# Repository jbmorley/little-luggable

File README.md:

# Little Luggable

Raspberry Pi Cyberdeck

## Overview

The Little Luggable is my take on a cyberdeck. It's built around the [Raspberry Pi 5](https://www.raspberrypi.com/products/raspberry-pi-5/) and the [Pelican 1150 Protector Case](https://www.peli.com/eu/en/product/cases/protector/1150). It includes a [fully-custom mechanical keyboard](/docs/keyboard) designed to perfectly fit the lid of the 1150.

Check out the [project page](https://little-luggable.jbmorley.co.uk) for more.

# License

Little Luggable is Copyright (c) 2022-2026 Jason Morley (see [COPYRIGHT](https://github.com/jbmorley/little-luggable/blob/main/COPYRIGHT)) and licensed under the [Creative Commons Attribution 4.0 International License](https://creativecommons.org/licenses/by/4.0/) (see [LICENSE](https://github.com/jbmorley/little-luggable/blob/main/LICENSE)). Unless otherwise stated, photographs are Copyright (c) 2026 [Mar Mizunaka](http://marmizunaka.com), and cannot be reproduced without permission.

The Little Luggable depends on the following separately licensed third-party libraries and components:

- [Keebio Components](https://github.com/keebio/keebio-components), MIT License
- [Keebio-Parts.pretty](https://github.com/keebio/Keebio-Parts.pretty), MIT License
- [marbastlib](https://github.com/ebastler/marbastlib), CERN Open Hardware Licence Version 2 – Permissive
- [Nabla](https://fonts.google.com/specimen/Nabla), SIL Open Font License 1.1
- [Recursive](https://fonts.google.com/specimen/Recursive), SIL Open Font License 1.1
- [ZMK](https://github.com/zmkfirmware/zmk), MIT License

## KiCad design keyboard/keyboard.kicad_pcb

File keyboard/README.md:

# Keyboard

## Design

The Little Luggable features a custom 64-key keyboard that I created with the very specific goal of deviating as little as possible from a standard keyboard layout.

The basic design was created using [Keyboard Layout Editor](http://www.keyboard-layout-editor.com) and the JSON can be found in `keyboard/layouts`.

### Base Layer

### Lower Layer (Bluetooth Controls)

### Raise Layer (Punctuation and Special Characters)

## Useful References

- [YouTube – Making a Keyboard Macropad PCB (Kicad 6.0), Noah Kiser](https://www.youtube.com/watch?v=7O8xGd7Pd88)
- [YouTube – Single Button Nice!Nano Keyboard, Ben Vallack](https://www.youtube.com/watch?v=vr8LkjsRqZs)
- [YouTube – Make your own analog keyboard PCB (in Kicad) - Part 1 (Schematic), riskable](https://www.youtube.com/watch?v=TfKz_FbZWLQ)
- [Broaching Standoff](https://www.youtube.com/watch?v=TuJRveLrtYI)
- [Broaching nuts and standoffs](https://www.inserco.eu/en/broaching-inserts-ipcbricbfhiscbr/)
- [Solderable threaded inserts?](https://www.designdevelopmenttoday.com/new-products/fastening-assembly/fastening-assembly/product/21092287/keystone-electronics-corp-zero-height-threaded-inserts-for-pc-boards)
- [Keyswitch Kicad Library](https://github.com/perigoso/keyswitch-kicad-library)

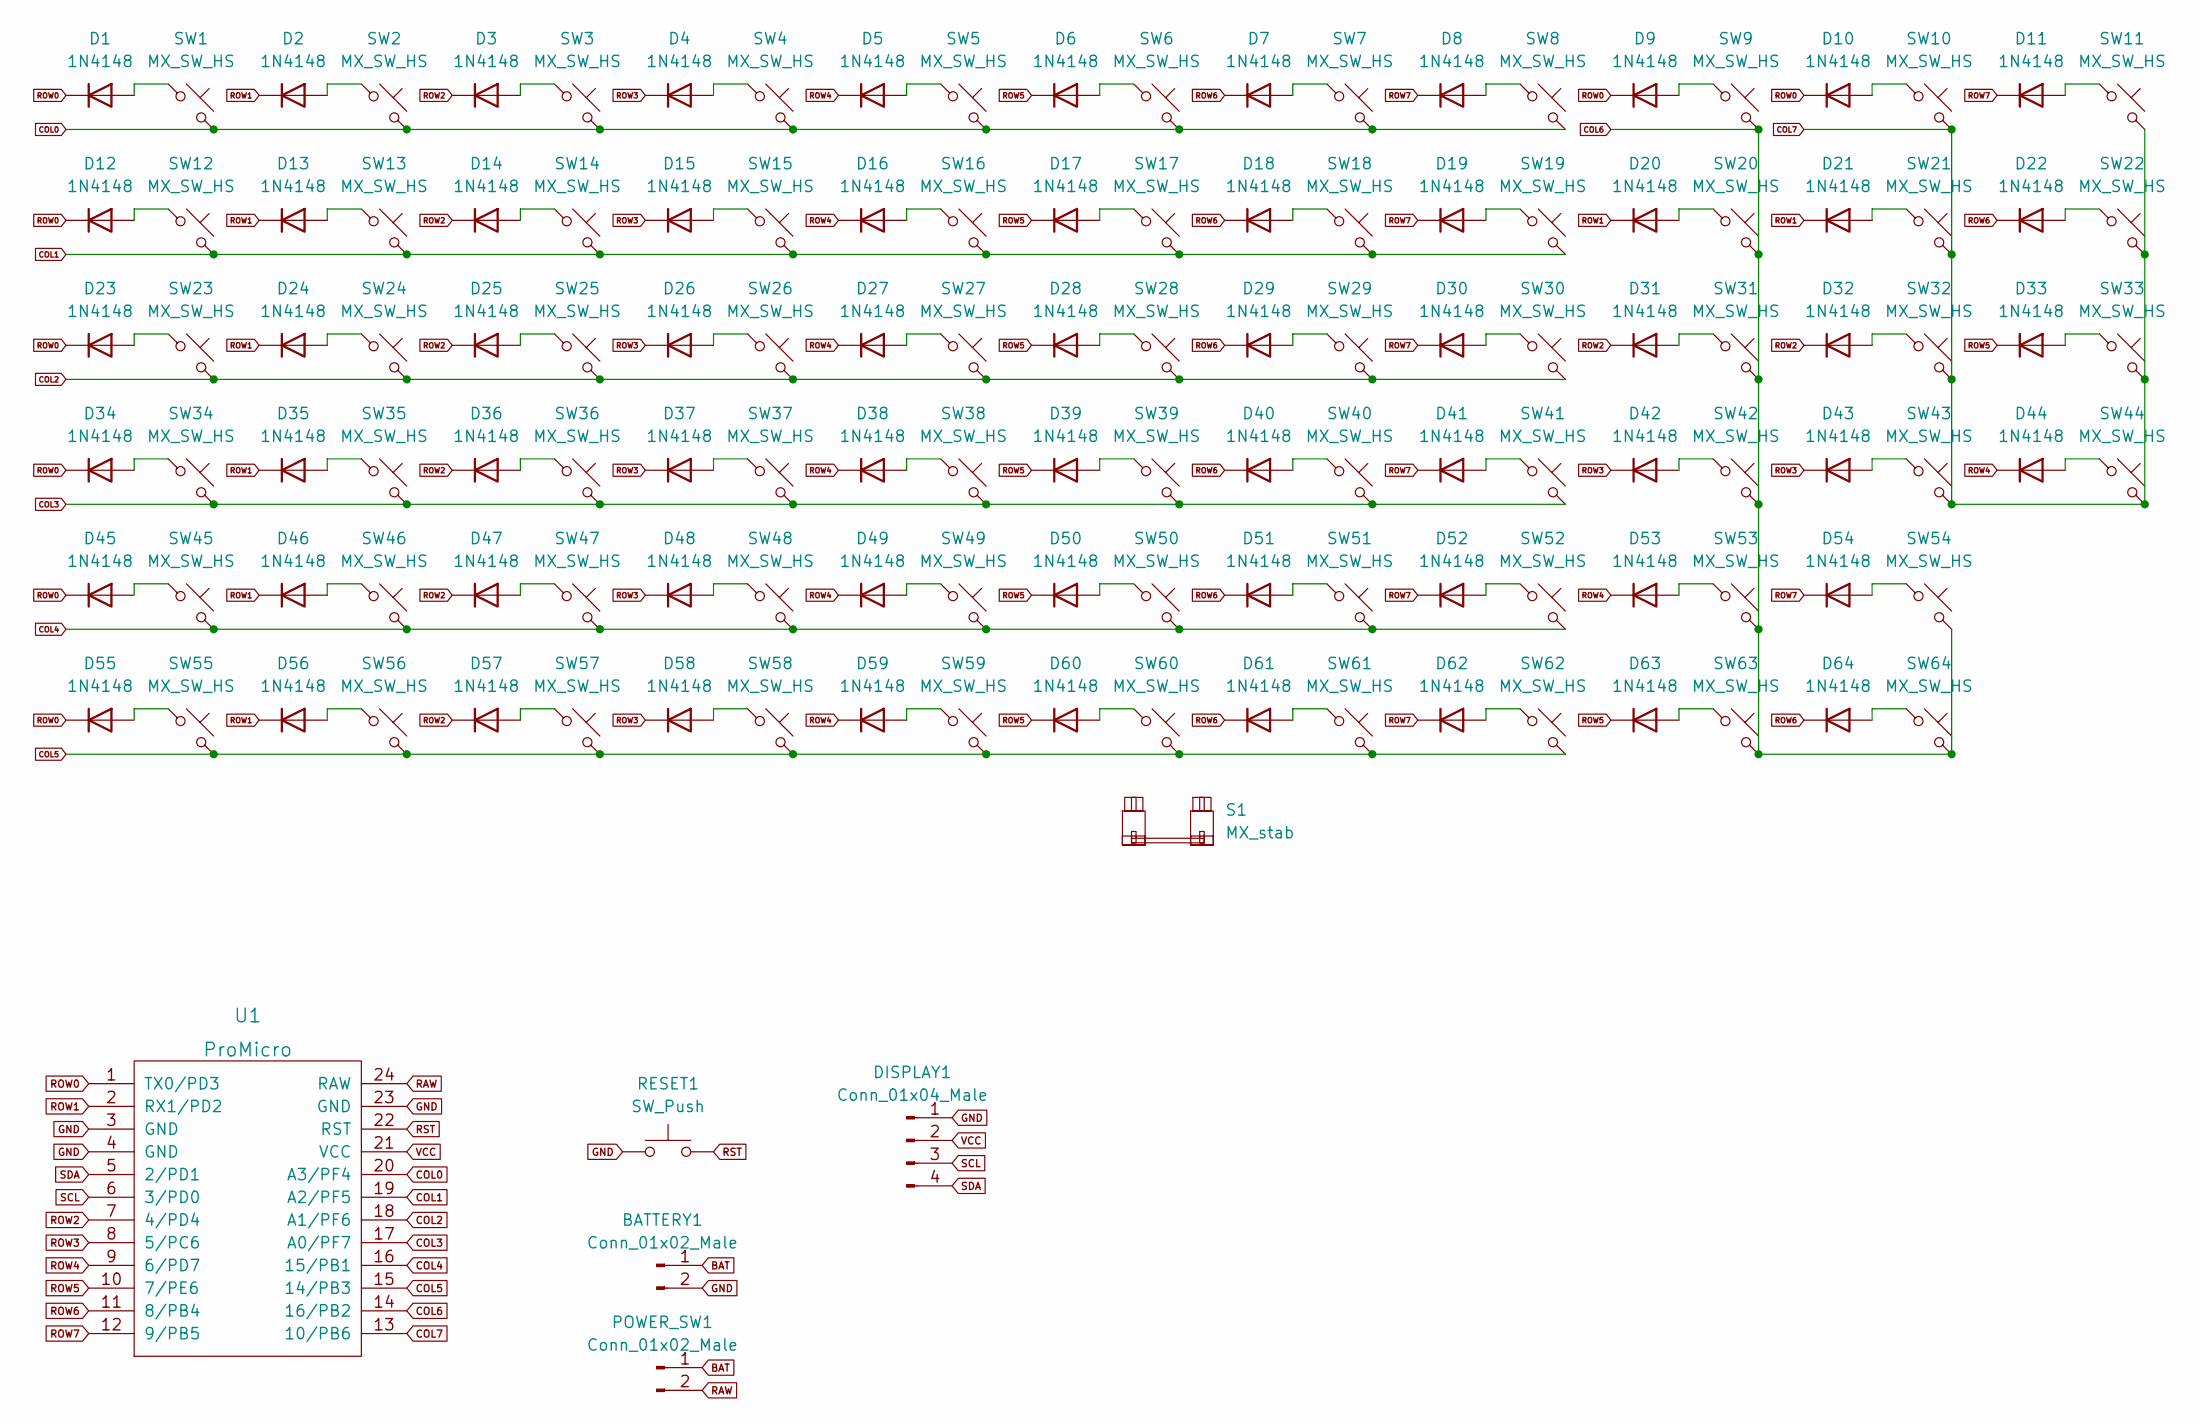
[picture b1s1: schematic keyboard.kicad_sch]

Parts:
BATTERY1: Conn_01x02_Male; PinHeader_1x02_P2.54mm_Vertical
D1, D2, D3, D4, D5, D6, D7, D8, D9, D10, D11, D12, D13, D14, D15, D16, D17, D18, D19, D20, D21, D22, D23, D24, D25, D26, D27, D28, D29, D30, D31, D32, D33, D34, D35, D36, D37, D38, D39, D40, D41, D42, D43, D44, D45, D46, D47, D48, D49, D50, D51, D52, D53, D54, D55, D56, D57, D58, D59, D60, D61, D62, D63, D64: 1N4148; D_DO-35_SOD27_P7.62mm_Horizontal
DISPLAY1: Conn_01x04_Male; PinHeader_1x04_P2.54mm_Vertical
POWER_SW1: Conn_01x02_Male; PinHeader_1x02_P2.54mm_Horizontal
RESET1: SW_Push; SW_PUSH_6mm_H13mm
S1: MX_stab; STAB_MX_P_2u
SW1, SW2, SW3, SW4, SW5, SW6, SW7, SW8, SW9, SW10, SW11, SW12, SW13, SW14, SW15, SW16, SW17, SW18, SW19, SW20, SW21, SW22, SW23, SW24, SW25, SW26, SW27, SW28, SW29, SW30, SW31, SW32, SW33, SW34, SW35, SW36, SW37, SW38, SW39, SW40, SW41, SW42, SW43, SW44, SW45, SW46, SW47, SW48, SW49, SW50, SW51, SW52, SW53, SW54, SW55, SW56, SW57, SW58, SW59, SW60, SW61, SW62, SW63, SW64: MX_SW_HS; SW_MX_HS_1u
U1: ProMicro; ArduinoProMicro

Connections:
BAT: BATTERY1.1, POWER_SW1.1; also elsewhere on the board
COL0: SW1.2, SW2.2, SW3.2, SW4.2, SW5.2, SW6.2, SW7.2, SW8.2, U1.20 (A3/PF4)
COL1: SW12.2, SW13.2, SW14.2, SW15.2, SW16.2, SW17.2, SW18.2, SW19.2, U1.19 (A2/PF5)
COL2: SW23.2, SW24.2, SW25.2, SW26.2, SW27.2, SW28.2, SW29.2, SW30.2, U1.18 (A1/PF6)
COL3: SW34.2, SW35.2, SW36.2, SW37.2, SW38.2, SW39.2, SW40.2, SW41.2, U1.17 (A0/PF7)
COL4: SW45.2, SW46.2, SW47.2, SW48.2, SW49.2, SW50.2, SW51.2, SW52.2, U1.16 (15/PB1)
COL5: SW55.2, SW56.2, SW57.2, SW58.2, SW59.2, SW60.2, SW61.2, SW62.2, U1.15 (14/PB3)
COL6: SW9.2, SW20.2, SW31.2, SW42.2, SW53.2, SW54.2, SW63.2, SW64.2, U1.14 (16/PB2)
COL7: SW10.2, SW11.2, SW21.2, SW22.2, SW32.2, SW33.2, SW43.2, SW44.2, U1.13 (10/PB6)
GND: BATTERY1.2, DISPLAY1.1, RESET1.1, U1.3 (GND), U1.4 (GND), U1.23 (GND); also elsewhere on the board
unnamed: D1.2 (A), SW1.1
unnamed: D2.2 (A), SW2.1
unnamed: D3.2 (A), SW3.1
unnamed: D4.2 (A), SW4.1
unnamed: D5.2 (A), SW5.1
unnamed: D6.2 (A), SW6.1
unnamed: D7.2 (A), SW7.1
unnamed: D8.2 (A), SW8.1
unnamed: D9.2 (A), SW9.1
unnamed: D10.2 (A), SW10.1
unnamed: D11.2 (A), SW11.1
unnamed: D12.2 (A), SW12.1
unnamed: D13.2 (A), SW13.1
unnamed: D14.2 (A), SW14.1
unnamed: D15.2 (A), SW15.1
unnamed: D16.2 (A), SW16.1
unnamed: D17.2 (A), SW17.1
unnamed: D18.2 (A), SW18.1
unnamed: D19.2 (A), SW19.1
unnamed: D20.2 (A), SW20.1
unnamed: D21.2 (A), SW21.1
unnamed: D22.2 (A), SW22.1
unnamed: D23.2 (A), SW23.1
unnamed: D24.2 (A), SW24.1
unnamed: D25.2 (A), SW25.1
unnamed: D26.2 (A), SW26.1
unnamed: D27.2 (A), SW27.1
unnamed: D28.2 (A), SW28.1
unnamed: D29.2 (A), SW29.1
unnamed: D30.2 (A), SW30.1
unnamed: D31.2 (A), SW31.1
unnamed: D32.2 (A), SW32.1
unnamed: D33.2 (A), SW33.1
unnamed: D34.2 (A), SW34.1
unnamed: D35.2 (A), SW35.1
unnamed: D36.2 (A), SW36.1
unnamed: D37.2 (A), SW37.1
unnamed: D38.2 (A), SW38.1
unnamed: D39.2 (A), SW39.1
unnamed: D40.2 (A), SW40.1
unnamed: D41.2 (A), SW41.1
unnamed: D42.2 (A), SW42.1
unnamed: D43.2 (A), SW43.1
unnamed: D44.2 (A), SW44.1
unnamed: D45.2 (A), SW45.1
unnamed: D46.2 (A), SW46.1
unnamed: D47.2 (A), SW47.1
unnamed: D48.2 (A), SW48.1
unnamed: D49.2 (A), SW49.1
unnamed: D50.2 (A), SW50.1
unnamed: D51.2 (A), SW51.1
unnamed: D52.2 (A), SW52.1
unnamed: D53.2 (A), SW53.1
unnamed: D54.2 (A), SW54.1
unnamed: D55.2 (A), SW55.1
unnamed: D56.2 (A), SW56.1
unnamed: D57.2 (A), SW57.1
unnamed: D58.2 (A), SW58.1
unnamed: D59.2 (A), SW59.1
unnamed: D60.2 (A), SW60.1
unnamed: D61.2 (A), SW61.1
unnamed: D62.2 (A), SW62.1
unnamed: D63.2 (A), SW63.1
unnamed: D64.2 (A), SW64.1
RAW: POWER_SW1.2, U1.24 (RAW); also elsewhere on the board
ROW0: D1.1 (K), D9.1 (K), D10.1 (K), D12.1 (K), D23.1 (K), D34.1 (K), D45.1 (K), D55.1 (K), U1.1 (TX0/PD3)
ROW1: D2.1 (K), D13.1 (K), D20.1 (K), D21.1 (K), D24.1 (K), D35.1 (K), D46.1 (K), D56.1 (K), U1.2 (RX1/PD2)
ROW2: D3.1 (K), D14.1 (K), D25.1 (K), D31.1 (K), D32.1 (K), D36.1 (K), D47.1 (K), D57.1 (K), U1.7 (4/PD4)
ROW3: D4.1 (K), D15.1 (K), D26.1 (K), D37.1 (K), D42.1 (K), D43.1 (K), D48.1 (K), D58.1 (K), U1.8 (5/PC6)
ROW4: D5.1 (K), D16.1 (K), D27.1 (K), D38.1 (K), D44.1 (K), D49.1 (K), D53.1 (K), D59.1 (K), U1.9 (6/PD7)
ROW5: D6.1 (K), D17.1 (K), D28.1 (K), D33.1 (K), D39.1 (K), D50.1 (K), D60.1 (K), D63.1 (K), U1.10 (7/PE6)
ROW6: D7.1 (K), D18.1 (K), D22.1 (K), D29.1 (K), D40.1 (K), D51.1 (K), D61.1 (K), D64.1 (K), U1.11 (8/PB4)
ROW7: D8.1 (K), D11.1 (K), D19.1 (K), D30.1 (K), D41.1 (K), D52.1 (K), D54.1 (K), D62.1 (K), U1.12 (9/PB5)
RST: RESET1.2, U1.22 (RST); also elsewhere on the board
SCL: DISPLAY1.3, U1.6 (3/PD0); also elsewhere on the board
SDA: DISPLAY1.4, U1.5 (2/PD1); also elsewhere on the board
VCC: DISPLAY1.2, U1.21 (VCC); also elsewhere on the board

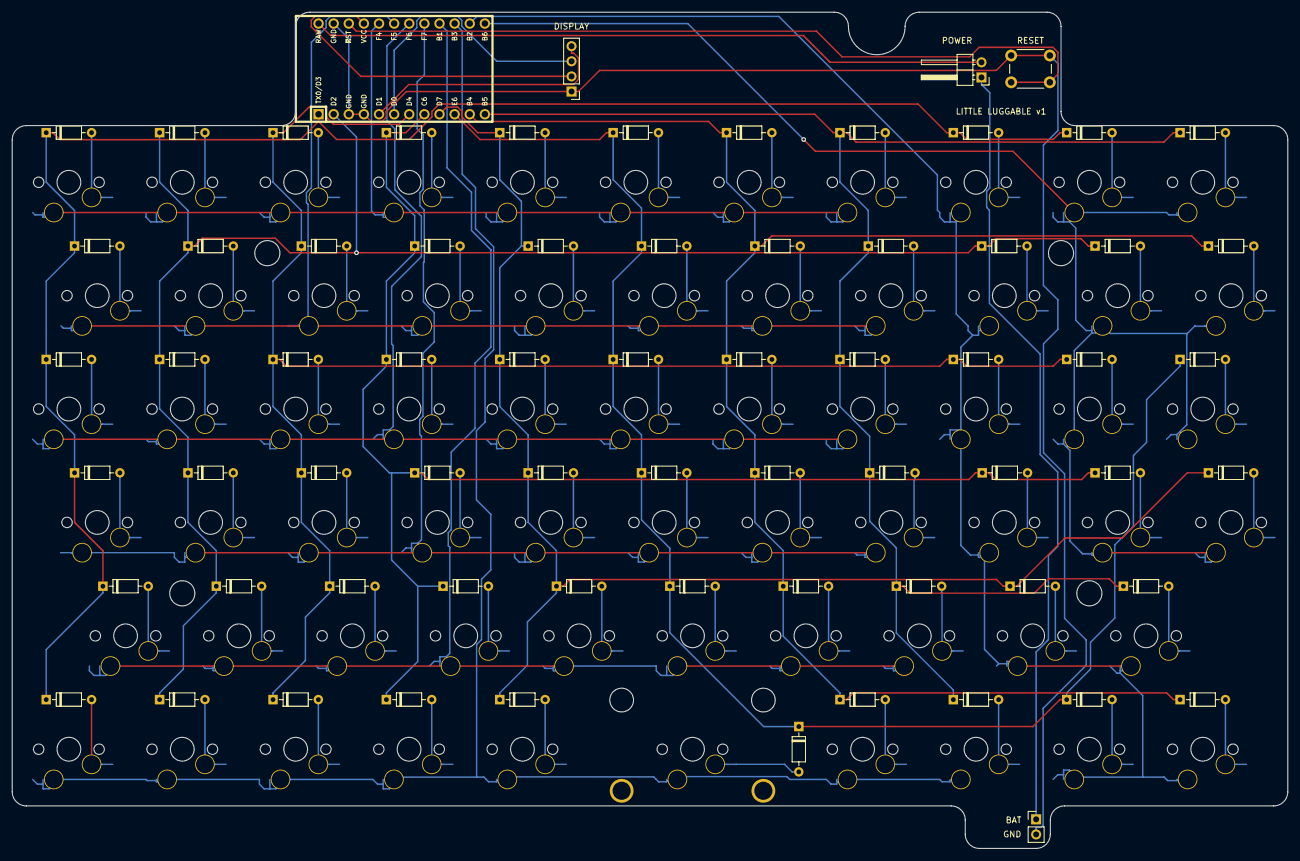
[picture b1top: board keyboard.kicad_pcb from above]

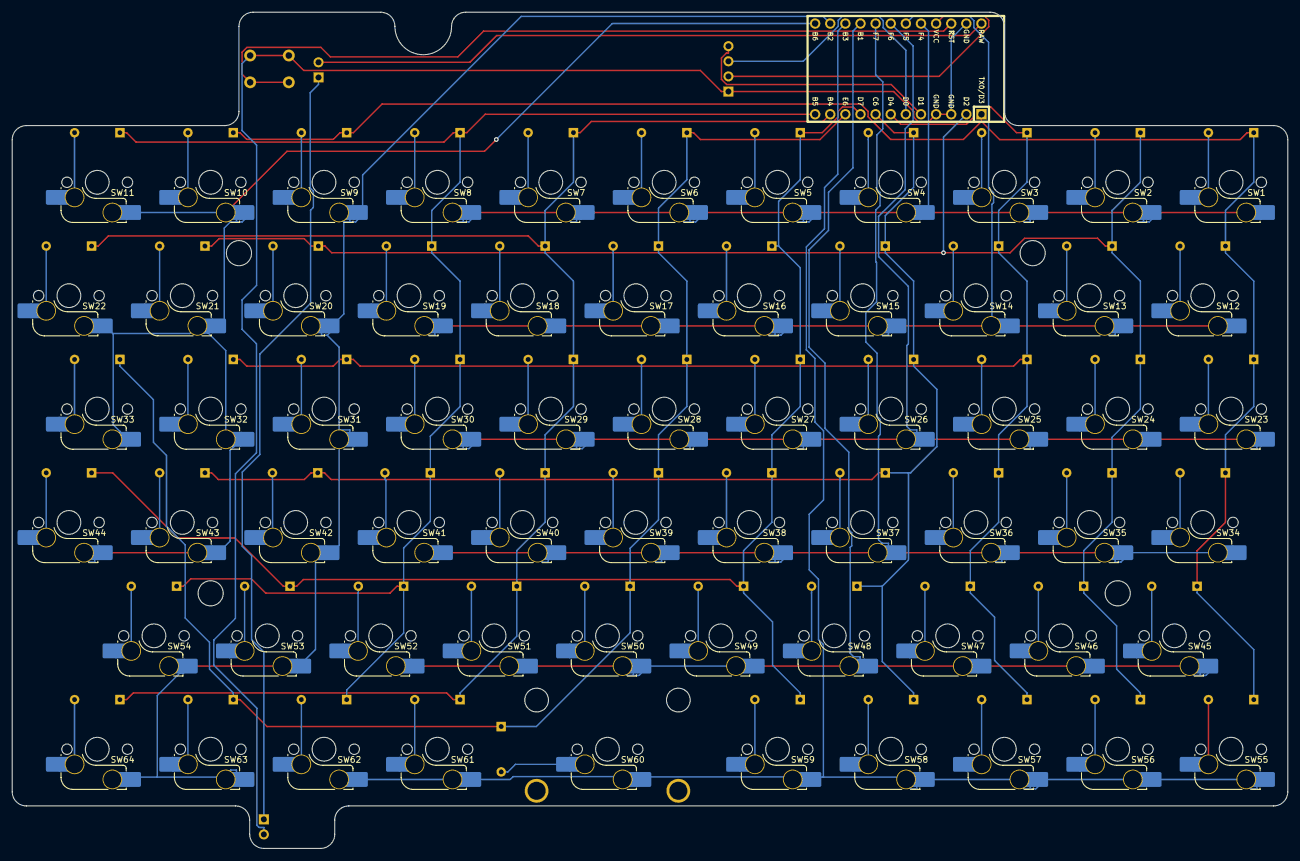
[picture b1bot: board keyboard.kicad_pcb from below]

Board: 2 copper layers, 214.3 x 140.5 mm, 134 parts (64 on the bottom side), 87 nets.

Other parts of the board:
DISPLAY: Conn_01x04_Male; PinHeader_1x04_P2.54mm_Vertical
POWER: Conn_01x02_Male; PinHeader_1x02_P2.54mm_Horizontal
RESET: SW_Push; SW_PUSH_6mm_H13mm

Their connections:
BAT: POWER.1; also elsewhere on the board
GND: DISPLAY.1, RESET.1; also elsewhere on the board
RAW: POWER.2; also elsewhere on the board
RST: RESET.2; also elsewhere on the board
SCL: DISPLAY.3; also elsewhere on the board
SDA: DISPLAY.4; also elsewhere on the board
VCC: DISPLAY.2; also elsewhere on the board

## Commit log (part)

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2023-02-15 Add the raise
2023-02-15 Correct the raise
2023-02-15 Add tilde
2023-02-16 Update the description and hero image
2023-02-16 Clean up the ideas
2023-02-16 Update the description
2023-02-16 Update the nice!nano link
2023-02-16 Clean up the keyboard parts table
2023-02-16 Clean up the main parts table
2023-02-16 Move some of the keyboard notes into a separate file
2023-02-16 Clearer 'Useful References' section
2023-02-16 Re-order the PiJuice and battery
2023-02-16 Add settings for laser cutting with Betsy
2023-02-16 Add footnote on laser cutter settings
2023-02-16 Add the keycaps
2023-02-16 Add the Kailh hotswap sockets
2023-02-16 Add brief description to the keyboard page
2023-02-16 Add a link to the keyswitch library
2023-02-16 Correct number of keycaps
2023-02-16 Add another YouTube video to the references
2023-02-16 Add a note on kerfing adjustments and additional step for checking the aluminium mounting plate
2023-02-16 Correct scaling for the export settings screenshot
2023-02-16 Add a header to the resources page
2023-02-16 Update the layout preview
2023-02-16 Correct scaling of the base layer
2023-02-16 Add the lower layer
2023-02-16 Add the lower layout
2023-02-16 Add the battery
2023-02-16 Add a link to Keyboard Layout Editor
2023-02-16 Simplify the BoM a little
2023-02-16 Add the Pi and display to the BoM
2023-02-16 Reorder the BoM
2023-02-17 Add CC license
2023-02-17 Flesh out the keyboard BOM
2023-02-17 Flesh out the keyboard parts
2023-02-17 Add computer parts
2023-02-17 Start moving the custom parts out
2023-02-17 Add the fascia image
2023-02-17 Link the project page
2023-02-17 Actually link the project
2023-02-17 Update the mounting plate image and add parts preamble
2023-02-17 Sensibly sized mounting plate
2023-02-17 Add larger render of the fascia
2023-02-17 Update the hero shot for something that shows the design off a little better
2023-02-17 Brighten the colors a little
2023-02-17 Slightly smaller image
2023-02-17 Add the fascia
2023-02-17 Change the orientation of the keyboard plate render
2023-02-17 Add keyboard mounting plate render
2023-02-17 Update the mounting plate render and add a link to the DXF
2023-02-17 Add links to the keyboard fascia dxf files
2023-02-17 Add updated keyboard fascia and pcb
2023-02-17 Add the keyboard assembly
2023-02-17 Update the hero and assembly
2023-02-17 Update the assembly and put it at the top of the keyboard section
2023-02-17 Link the switch collar dxf file
2023-02-17 Add a note on making your own
2023-02-17 Add the screen assembly render
2023-02-17 Update future heading
2023-02-17 Add keyboard mounting brackets
2023-02-17 Clean up the links to the DXF files
2023-02-17 Add note on generating renders
2023-02-17 Add notes on sharing the design files
2023-02-17 Don't stretch out the list
2023-02-17 Update the screen part renders to match the projection of the screen
2023-02-17 Link to mogrify
2023-02-17 Add links to the keystones
2023-02-17 Move the screen renders to a subdirectory
2023-02-17 Move the keyboard renders to a subdirectory
2023-02-19 Add additional special keys
2023-02-19 Add the semi-colon and apostrophe
2023-02-19 Add left bracket, right bracket, and backslash
2023-02-19 Add <>,
2023-02-19 Mod-morph experiment
2023-02-19 Remove errant brace
2023-02-19 Try adding a dot/question key
2023-02-19 This might be necessary
2023-02-19 Support left and right shift on the upper layer
2023-02-19 Remove graveesc and add the modifiers back into the raised layer
2023-02-19 Add additional special keys (#2)
    This change fleshes out the raised layer, adding support for all the
    standard US-en keys that are omitted on the default layer. It also
    adjusts the behaviour of the key to the left of right-shift to make it
    DOT and QUESTION by default.
2023-02-19 Add F11 and F12 to the raised layer and document the raised layer
2023-02-19 Add F11 and F12 to the raised layer and document the raised layer (#3)
2023-02-21 Update the latest manufacture files
2023-02-21 Update the latest manufacture files (#4)
2023-02-21 Clean up the list of future ideas
2023-02-21 Remove the future ideas section now these are GitHub issues
2023-02-22 Add a forward slash to the keyboard
2023-02-22 Update the keymap previews
2023-02-22 Add a forward slash to the keyboard (#15)
2023-02-24 Add keyboard mounting plate diagram
2023-02-24 Add screws and nuts
2023-02-24 Add manufacture files
2023-02-24 Remove legacy manufacture files to simplify things
2023-03-17 fix(keyboard): Map space on the upper layer
2023-03-17 fix(keyboard): Map space on the upper layer (#18)
2023-03-21 fix: Improve Bluetooth reliability
2024-03-20 Include the schematics for the Geekworm X1202 UPS power board
2024-03-25 Add the kerf-adjusted fascias
2024-03-25 Add the mounting brackets
2024-04-12 Add the complete keyboard layout to the readme for easy reference
2025-10-07 fix: Add builds for nice!nano v1
2026-03-28 fix: Add builds for nice!nano v1 (#21)
